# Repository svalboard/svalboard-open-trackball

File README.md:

The Svalboard Open Trackball design builds on the SideraKB PMW3360 design to make it more compact and usable for any trackball application.
This is the bare minimum footprint achievable in a single-sided SMT assembly ready to receive hand-soldered PMW3389/60 parts -- it is intended to be ordered direct from JLCPCB, fully assembled except for the PMW part, which you'll need to source and hand solder.

Note that in this design 3389 is the default sensor -- you need to cut and bridge the jumper for PMW3360.
Turns out PMW3389 is cheaper to buy on Aliexpress anyway... :D

By trimming lenses to match the footprint, you can fit these sensors in places previously not possible.
Because they're derived from the SideraKB version, these PCBAs are released under CERN OHL 2P, a permissive open hardware license.
I don't want to restrict what you do in any way, but since Sidera used this license, its terms still apply.

No support is offered for this design, please don't bug me (:

Note: May 20, 2024
The Svalboard Open Trackball Onshape repo is permalinked at www.svalboard.com/trackball-repo
Feel free to copy that repo and use it for whatever you like.
It will eventually include CAD for trackballs using this PCBA -- currently WIP.

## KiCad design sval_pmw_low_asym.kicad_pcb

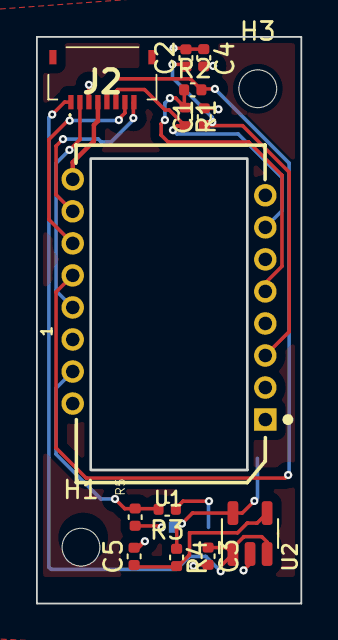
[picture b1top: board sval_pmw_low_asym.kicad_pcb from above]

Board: 4 copper layers, 14.6 x 31.4 mm, 16 parts (1 on the bottom side), 15 nets.

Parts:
C1: 4.7uF/10V; C_0402_1005Metric
C2: 100nF; C_0402_1005Metric
C3, C4: 1uF; C_0402_1005Metric
C5: 22nF; C_0402_1005Metric
H1, H3: MountingHole_Pad; MountingHole_2.1mm
J2: Conn_01x08; FH34SRJ8S05SH50
JP2: SolderJumper_3_Bridged12; SolderJumper-3_P1.3mm_Bridged12_RoundedPad1.0x1.5mm_NumberL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
R1: 10k; R_0402_1005Metric
R2: 10k; C_0402_1005Metric
R3: 39R; C_0402_1005Metric
R4: 28k; C_0402_1005Metric
R5: 13R; C_0402_1005Metric
U1: PMW3360; PMW3360DM-T2QU 16Pin
U2: TLV74318PDBVR; SOT-23-5

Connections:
/CS: J2.2, U1.13 (~CS)
/MISO: J2.5, R2.2, U1.12 (MISO)
/MOSI: J2.7, U1.11 (MOSI)
/MOTION: J2.4, U1.9 (MOTION)
/RESET: J2.6, R1.2, U1.7 (~RESET)
/SCLK: J2.8, U1.10 (SCLK)
GND: C1.2, C2.2, C3.2, C4.2, C5.2, J2.3, U1.8 (GND), U2.2 (GND)
unnamed: JP2.1 (A), R5.2
unnamed: JP2.3 (B), R3.1
unnamed: R3.2, R5.1, U1.15 (LED_P)
unnamed: C1.1, C2.1, U1.3 (VDDPIX)
unnamed: C5.1, R4.2, U2.4 (NC)
VDD: C4.1, JP2.2 (C), R4.1, U1.4 (VDD), U2.5 (OUT)
V_{IN}: C3.1, J2.1, U2.1 (IN), U2.3 (EN)
V_{IO}: R1.1, R2.1, U1.5 (VDDIO)

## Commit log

2024-05-20 on main
